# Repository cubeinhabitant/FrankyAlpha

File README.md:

# FrankyAlpha
First prop controller: 4 inputs, 4 outputs.

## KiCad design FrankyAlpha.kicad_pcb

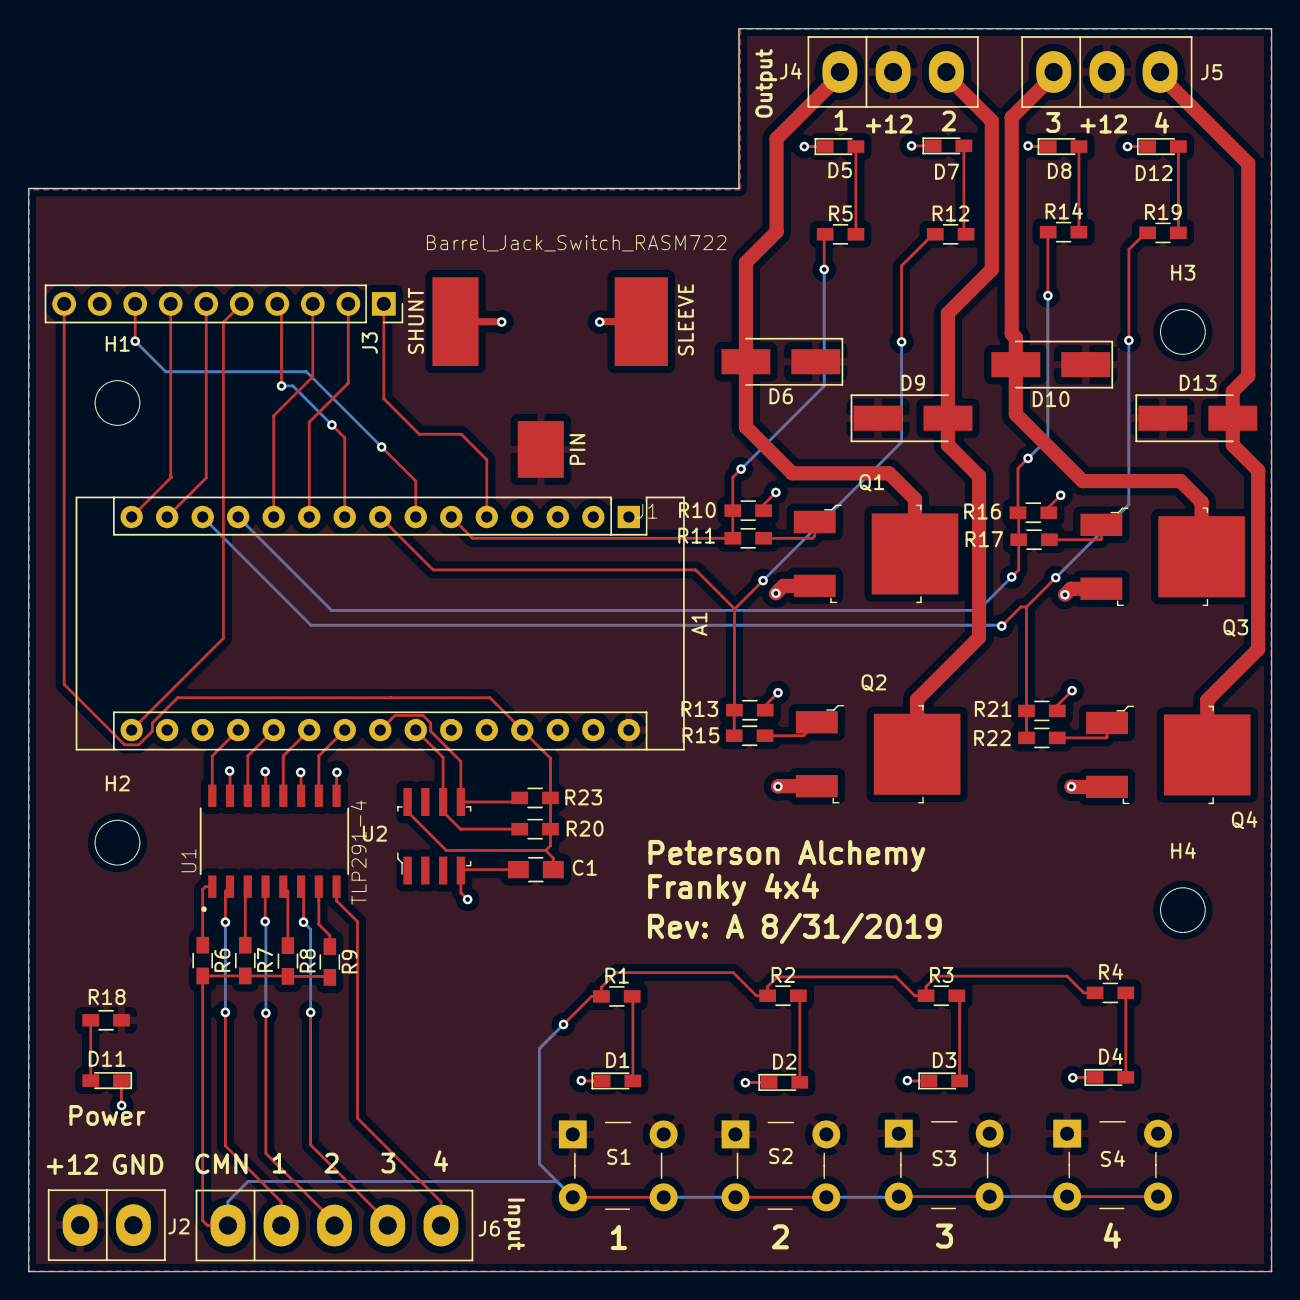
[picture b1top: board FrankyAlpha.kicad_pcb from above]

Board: 2 copper layers, 88.9 x 88.9 mm, 58 parts (0 on the bottom side), 47 nets.

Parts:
A1: Arduino_Nano_v3.x; Arduino_Nano
C1: 10uF; C_0805_HandSoldering
D1, D2, D3, D4: LED ORANGE; LED_0603_HandSoldering
D5, D7, D8, D12: LED GREEN; LED_0603_HandSoldering
D6, D9, D10, D13: D_Schottky; D_SMA_Handsoldering
D11: LED RED; LED_0603_HandSoldering
H1, H2, H3, H4: MountingHole; MountingHole_3.2mm_M3
J1: Barrel_Jack_Switch_RASM722; SWITCHCRAFT_RASM722X_Pin_Numbers
J2: Conn_01x02; TerminalBlock-3.81-01x02
J3: Conn_01x10_Male; PinSocket_1x10_P2.54mm_Vertical
J4, J5: Conn_01x03; TerminalBlock-3.81-01x03
J6: Conn_01x05; TerminalBlock-3.81-01x05
Q1, Q2, Q3, Q4: FQD13N06L; TO-252-3
R1, R2, R3, R4, R18: 560; R_0603_HandSoldering
R5, R12, R14, R19: 330; R_0603_HandSoldering
R6, R7, R8, R9: 220; R_0603_HandSoldering
R10, R11, R13, R15, R16, R17, R21, R22: 10K; R_0603_HandSoldering
R20, R23: 4.7K; R_0603_HandSoldering
S1, S2, S3, S4: B3F-1000; Switch_Tactile_THT_B3F-1xxx
U1: TLP291-4; SOIC127P700X229-16N
U2: MB85RC256VPF-G-JNERE2; SOIC-8_W3.9mm

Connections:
+5V: A1.27, C1.1, J3.10, R20.1, R23.1, U2.8
+12V: A1.30, D6.1, D9.1, D10.1, D13.1, J1.1, J2.1, J4.2, J5.2, R18.1, S1.1, S1.2, S2.1, S2.2, S3.1, S3.2, S4.1, S4.2
/CS: A1.7, J3.8
/DREQ: A1.5, J3.1
/DataOutput1PWM: A1.6, R5.1, R10.1, R11.2
/DataOutput2PWM: A1.8, R12.1, R13.1, R15.2
/DataOutput3PWM: A1.12, R14.1, R16.1, R17.2
/DataOutput4PWM: A1.13, R19.1, R21.1, R22.2
/Input1: J6.2, U1.2
/Input2: J6.3, U1.4
/Input3: J6.4, U1.6
/Input4: J6.5, U1.8
/InputCommon: J6.1, R1.1, R2.1, R3.1, R4.1, R6.2, R7.2, R8.2, R9.2, S1.3, S1.4, S2.3, S2.4, S3.3, S3.4, S4.3, S4.4
/MISO: A1.15, J3.7
/MOSI: A1.14, J3.6
/OutputGnd1: D6.2, J4.1, Q1.4
/OutputGnd2: D9.2, J4.3, Q2.4
/OutputGnd3: D10.2, J5.1, Q3.4
/OutputGnd4: D13.2, J5.3, Q4.4
/SCK: A1.16, J3.5
/SCL: A1.24, R20.2, U2.6
/SDA: A1.23, R23.2, U2.5
/TriggerDigital1: A1.19, U1.16
/TriggerDigital2: A1.20, U1.14
/TriggerDigital3: A1.21, U1.12
/TriggerDigital4: A1.22, U1.10
/XCS: A1.9, J3.4
/XDCS: A1.10, J3.2
/XRESET: A1.11, J3.3
GND: A1.4, A1.29, C1.2, D1.1, D2.1, D3.1, D4.1, D5.1, D7.1, D8.1, D11.1, D12.1, J1.2, J1.3, J2.2, J3.9, Q1.3, Q2.3, Q3.3, Q4.3, R10.2, R13.2, R16.2, R21.2, U1.9, U1.11, U1.13, U1.15, U2.4
unnamed: D1.2, R1.2
unnamed: D2.2, R2.2
unnamed: D3.2, R3.2
unnamed: D4.2, R4.2
unnamed: D5.2, R5.2
unnamed: D7.2, R12.2
unnamed: D8.2, R14.2
unnamed: D11.2, R18.2
unnamed: D12.2, R19.2
unnamed: Q1.1, R11.1
unnamed: Q2.1, R15.1
unnamed: Q3.1, R17.1
unnamed: Q4.1, R22.1
unnamed: R6.1, U1.1
unnamed: R7.1, U1.3
unnamed: R8.1, U1.5
unnamed: R9.1, U1.7

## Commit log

2019-09-04 Rev: A
